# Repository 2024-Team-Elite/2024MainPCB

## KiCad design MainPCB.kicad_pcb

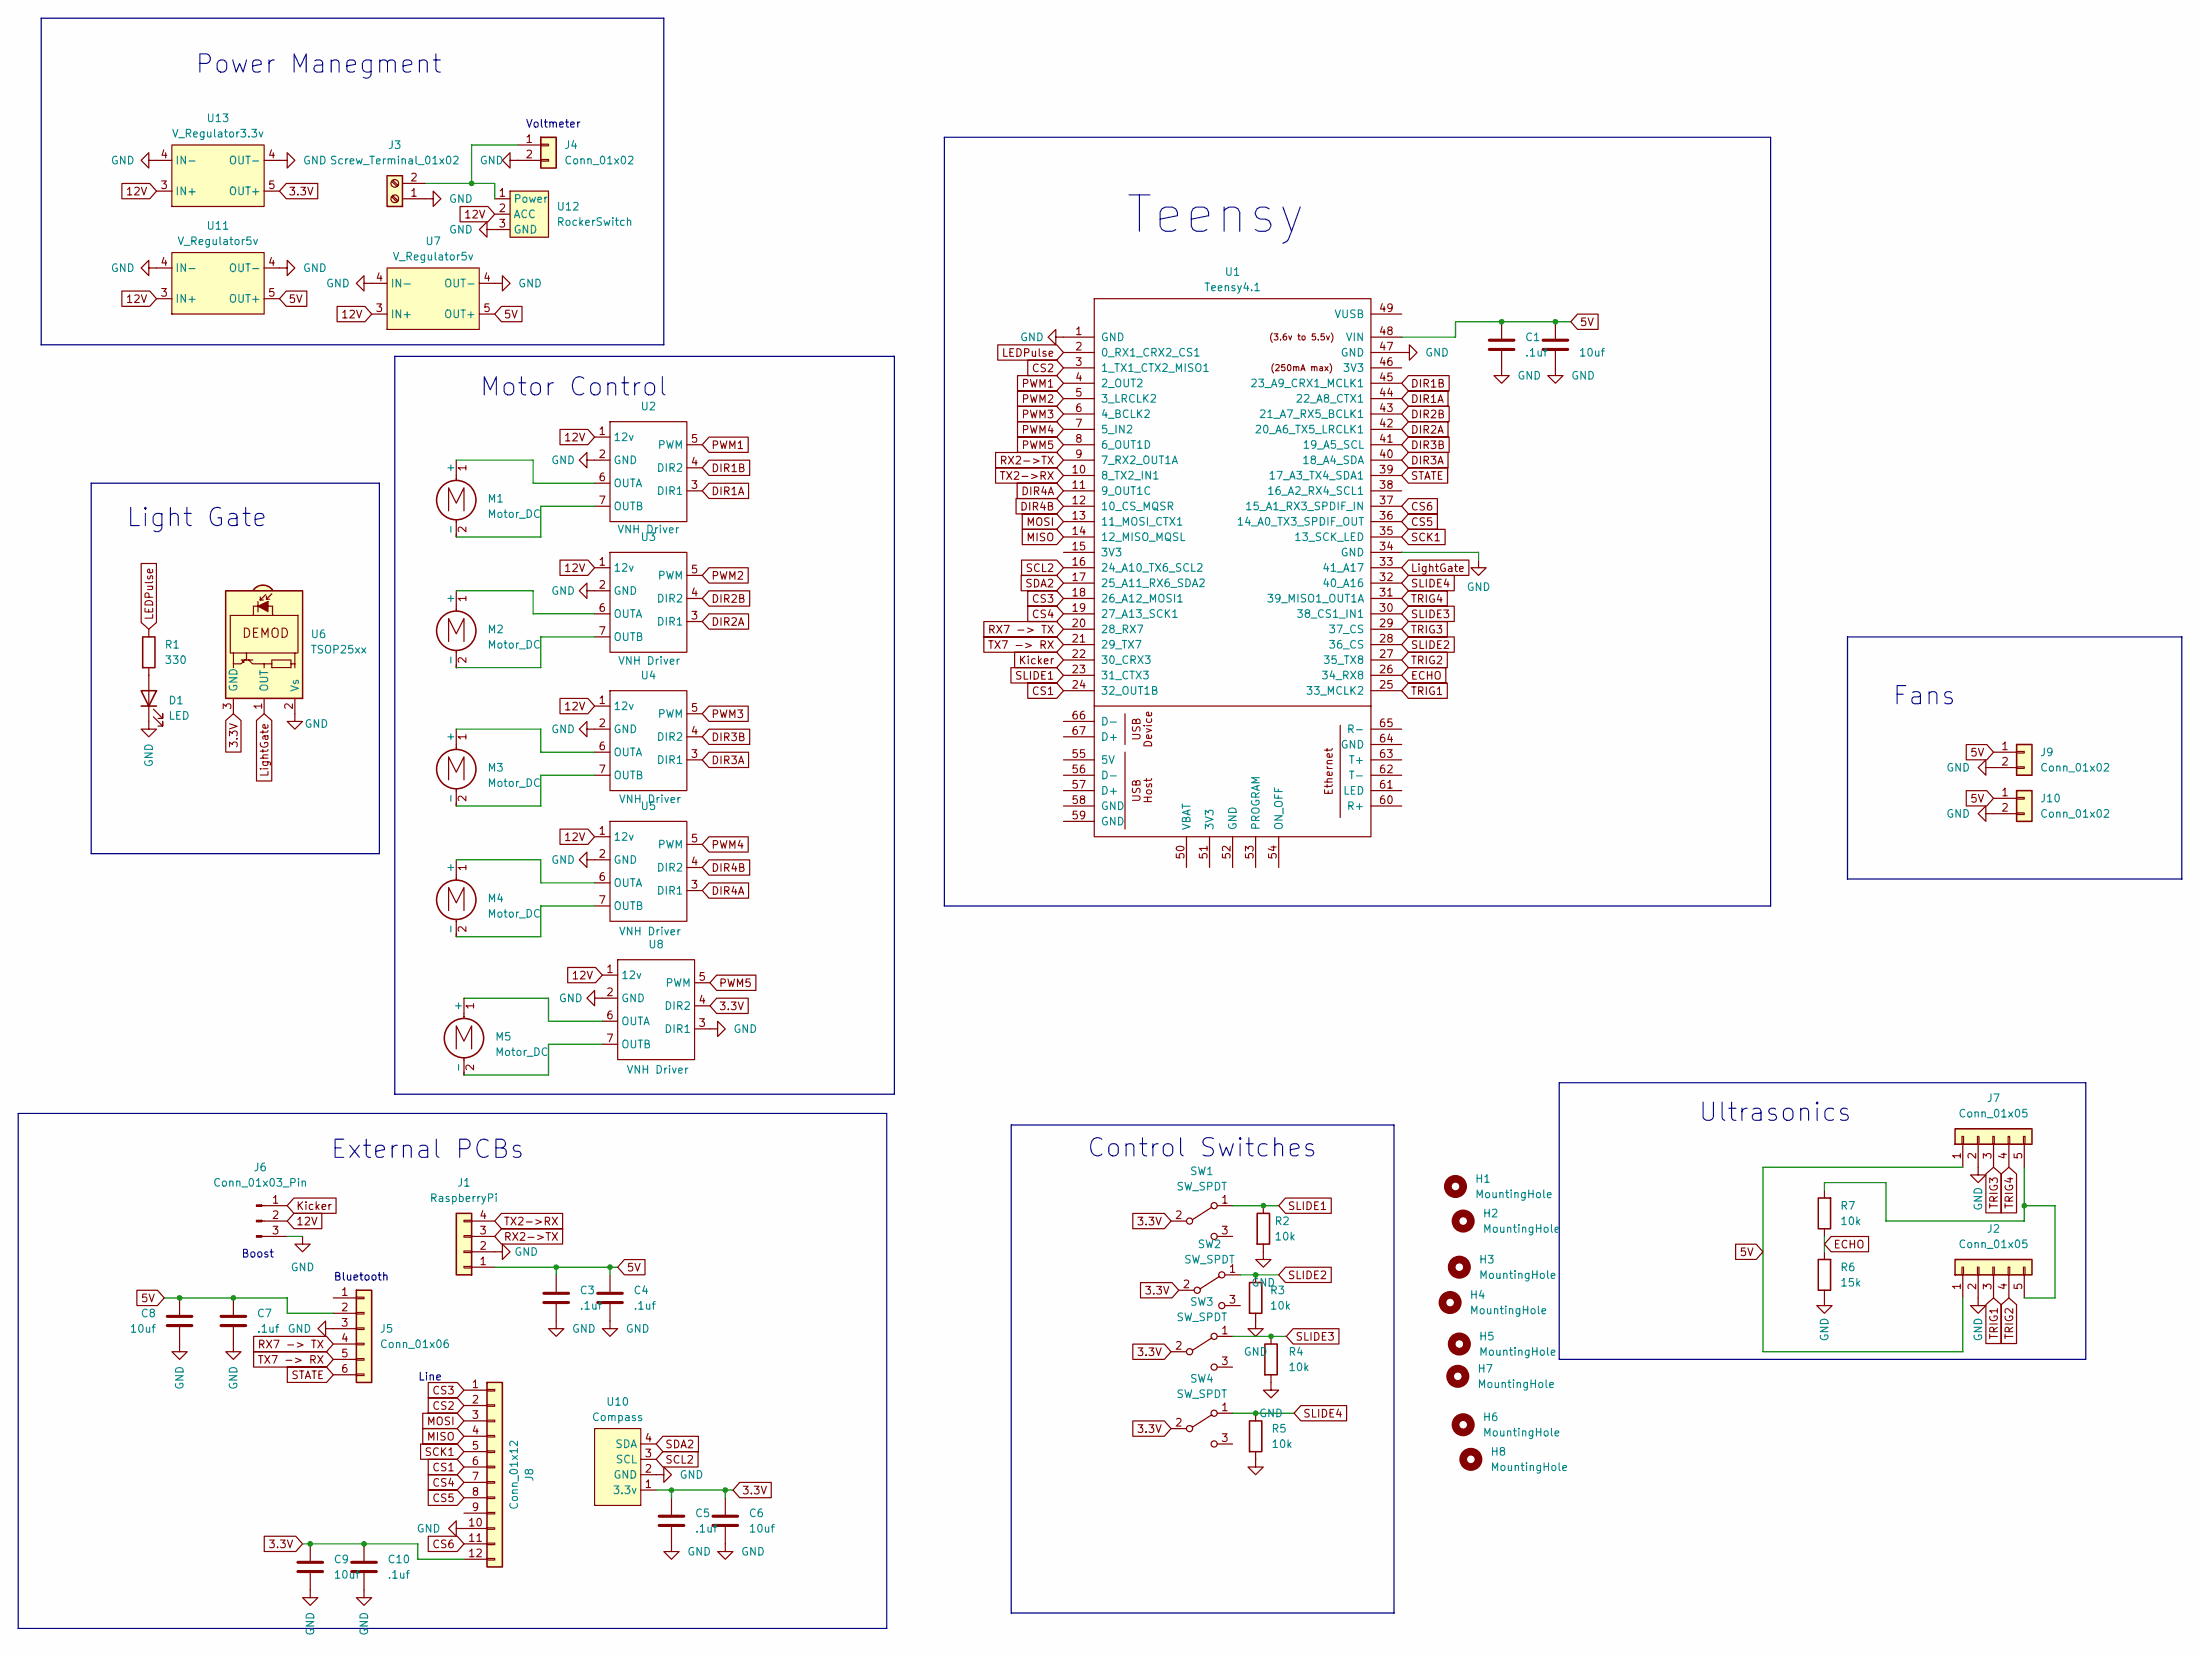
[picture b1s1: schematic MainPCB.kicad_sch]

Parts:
C1, C3, C4, C5, C7, C10: .1uf; C_0805_2012Metric
C2, C6, C8, C9: 10uf; C_0805_2012Metric
D1: LED; JST_XH_B2B-XH-AM_1x02_P2.50mm_Vertical
H1, H2, H3, H4, H5, H6, H7, H8: MountingHole; MountingHole_3.2mm_M3_DIN965_Pad
J1: RaspberryPi; JST_XH_B4B-XH-AM_1x04_P2.50mm_Vertical
J2, J7: Conn_01x05; JST_XH_B5B-XH-A_1x05_P2.50mm_Vertical
J3: Screw_Terminal_01x02; AMASS_XT60-F_1x02_P7.20mm_Vertical
J4: Conn_01x02; PinHeader_2x01_P2.54mm_Vertical
J5: Conn_01x06; PinHeader_1x06_P2.54mm_Vertical
J6: Conn_01x03_Pin; JST_XH_B3B-XH-AM_1x03_P2.50mm_Vertical
J8: Conn_01x12; IDC-Header_2x06_P2.54mm_Vertical
J9, J10: Conn_01x02; PinHeader_1x02_P2.54mm_Vertical
M1, M2, M3, M4, M5: Motor_DC; JST_XH_B2B-XH-AM_1x02_P2.50mm_Vertical
R1: 330; R_Axial_DIN0207_L6.3mm_D2.5mm_P10.16mm_Horizontal
R2, R3, R4, R5: 10k; C_0805_2012Metric_Pad1.18x1.45mm_HandSolder
R6: 15k; C_0805_2012Metric
R7: 10k; C_0805_2012Metric
SW1, SW2, SW3, SW4: SW_SPDT; SPDT_OS102011_CNK
U1: Teensy4.1; Teensy41
U2, U3, U4, U5, U8: VNH Driver; VNHDriver
U6: TSOP25xx; JST_XH_B3B-XH-AM_1x03_P2.50mm_Vertical
U7: V_Regulator5v; Pololu Regulator
U10: Compass; Compass Sensor DFRobot
U11: V_Regulator5v; Pololu5V3.4A
U12: RockerSwitch; RF1-1A-DC-2-B-2
U13: V_Regulator3.3v; Pololu Regulator

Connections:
3.3V: C5.1, C6.1, C9.1, C10.1, J8.12, SW1.2 (B), SW2.2 (B), SW3.2 (B), SW4.2 (B), U6.3 (GND), U8.4 (DIR2), U10.1 (3.3v), U13.5 (OUT+)
5V: C1.1, C2.1, C3.1, C4.1, C7.1, C8.1, J1.1, J2.1, J5.2, J7.1, J9.1, J10.1, U1.48 (VIN), U7.5 (OUT+), U11.5 (OUT+)
12V: J6.2, U2.1 (12v), U3.1 (12v), U4.1 (12v), U5.1 (12v), U7.3 (IN+), U8.1 (12v), U11.3 (IN+), U12.2 (ACC), U13.3 (IN+)
CS1: J8.6, U1.24 (32_OUT1B)
CS2: J8.2, U1.3 (1_TX1_CTX2_MISO1)
CS3: J8.1, U1.18 (26_A12_MOSI1)
CS4: J8.7, U1.19 (27_A13_SCK1)
CS5: J8.8, U1.36 (14_A0_TX3_SPDIF_OUT)
CS6: J8.11, U1.37 (15_A1_RX3_SPDIF_IN)
DIR1A: U1.44 (22_A8_CTX1), U2.3 (DIR1)
DIR1B: U1.45 (23_A9_CRX1_MCLK1), U2.4 (DIR2)
DIR2A: U1.42 (20_A6_TX5_LRCLK1), U3.3 (DIR1)
DIR2B: U1.43 (21_A7_RX5_BCLK1), U3.4 (DIR2)
DIR3A: U1.40 (18_A4_SDA), U4.3 (DIR1)
DIR3B: U1.41 (19_A5_SCL), U4.4 (DIR2)
DIR4A: U1.11 (9_OUT1C), U5.3 (DIR1)
DIR4B: U1.12 (10_CS_MQSR), U5.4 (DIR2)
ECHO: R6.2, R7.1, U1.26 (34_RX8)
GND: C1.2, C2.2, C3.2, C4.2, C5.2, C6.2, C7.2, C8.2, C9.2, C10.2, D1.1 (K), J1.2, J2.2, J3.1, J4.2, J5.3, J6.3, J7.2, J8.10, J9.2, J10.2, R2.2, R3.2, R4.2, R5.2, R6.1, U1.1 (GND), U1.34 (GND), U1.47 (GND), U2.2 (GND), U3.2 (GND), U4.2 (GND), U5.2 (GND), U6.2 (Vs), U7.4 (IN-), U8.2 (GND), U8.3 (DIR1), U10.2 (GND), U11.4 (IN-), U12.3 (GND), U13.4 (OUT-)
Kicker: J6.1, U1.22 (30_CRX3)
LEDPulse: R1.1, U1.2 (0_RX1_CRX2_CS1)
LightGate: U1.33 (41_A17), U6.1 (OUT)
MISO: J8.4, U1.14 (12_MISO_MQSL)
MOSI: J8.3, U1.13 (11_MOSI_CTX1)
unnamed: D1.2 (A), R1.2
unnamed: J2.5, J7.5, R7.2
unnamed: J3.2, J4.1, U12.1 (Power)
unnamed: M1.1 (+), U2.6 (OUTA)
unnamed: M1.2 (-), U2.7 (OUTB)
unnamed: M2.1 (+), U3.6 (OUTA)
unnamed: M2.2 (-), U3.7 (OUTB)
unnamed: M3.1 (+), U4.6 (OUTA)
unnamed: M3.2 (-), U4.7 (OUTB)
unnamed: M4.1 (+), U5.6 (OUTA)
unnamed: M4.2 (-), U5.7 (OUTB)
unnamed: M5.1 (+), U8.6 (OUTA)
unnamed: M5.2 (-), U8.7 (OUTB)
PWM1: U1.4 (2_OUT2), U2.5 (PWM)
PWM2: U1.5 (3_LRCLK2), U3.5 (PWM)
PWM3: U1.6 (4_BCLK2), U4.5 (PWM)
PWM4: U1.7 (5_IN2), U5.5 (PWM)
PWM5: U1.8 (6_OUT1D), U8.5 (PWM)
RX2->TX: J1.3, U1.9 (7_RX2_OUT1A)
RX7 -> TX: J5.4, U1.20 (28_RX7)
SCK1: J8.5, U1.35 (13_SCK_LED)
SCL2: U1.16 (24_A10_TX6_SCL2), U10.3 (SCL)
SDA2: U1.17 (25_A11_RX6_SDA2), U10.4 (SDA)
SLIDE1: R2.1, SW1.1 (A), U1.23 (31_CTX3)
SLIDE2: R3.1, SW2.1 (A), U1.28 (36_CS)
SLIDE3: R4.1, SW3.1 (A), U1.30 (38_CS1_IN1)
SLIDE4: R5.1, SW4.1 (A), U1.32 (40_A16)
STATE: J5.6, U1.39 (17_A3_TX4_SDA1)
TRIG1: J2.3, U1.25 (33_MCLK2)
TRIG2: J2.4, U1.27 (35_TX8)
TRIG3: J7.3, U1.29 (37_CS)
TRIG4: J7.4, U1.31 (39_MISO1_OUT1A)
TX2->RX: J1.4, U1.10 (8_TX2_IN1)
TX7 -> RX: J5.5, U1.21 (29_TX7)

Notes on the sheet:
Line
Fans
Voltmeter
Light Gate
Ultrasonics
External PCBs
Boost
Control Switches
Teensy
Bluetooth
Power Manegment
Motor Control

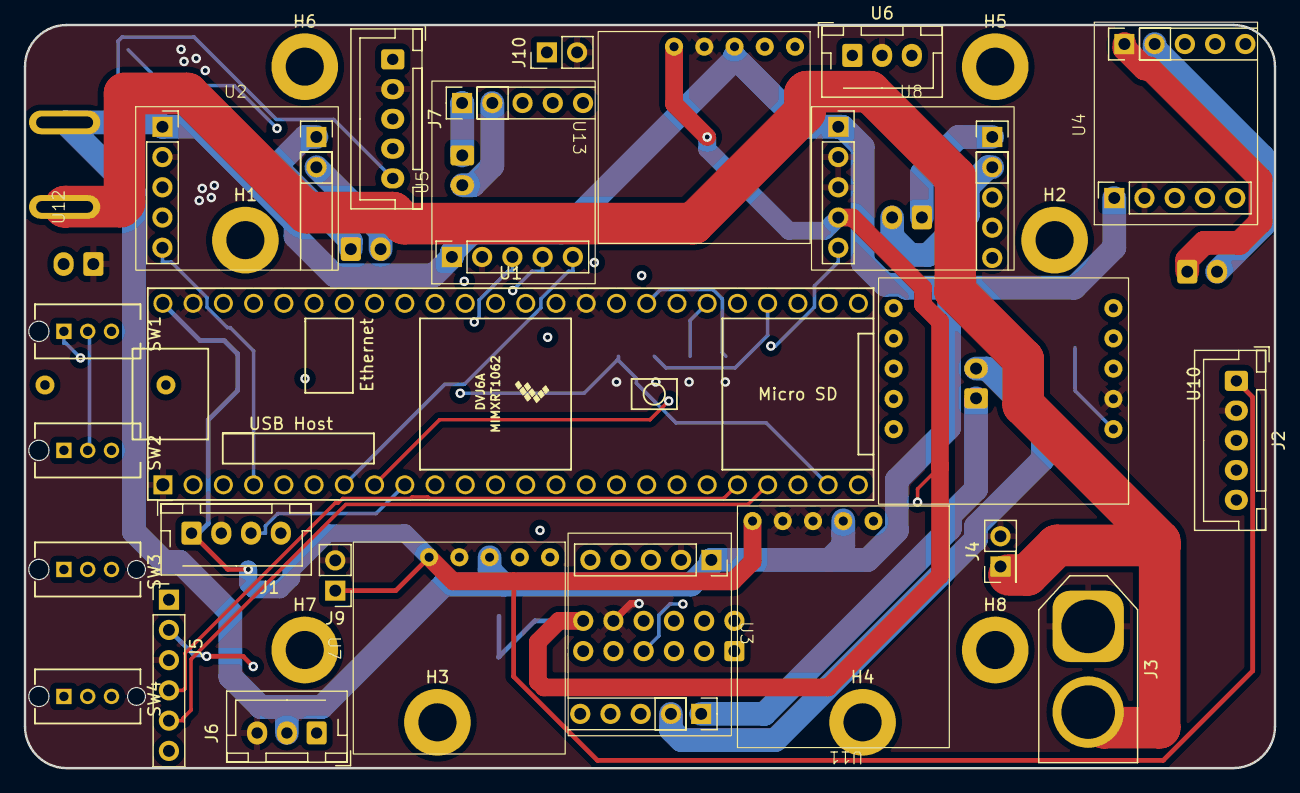
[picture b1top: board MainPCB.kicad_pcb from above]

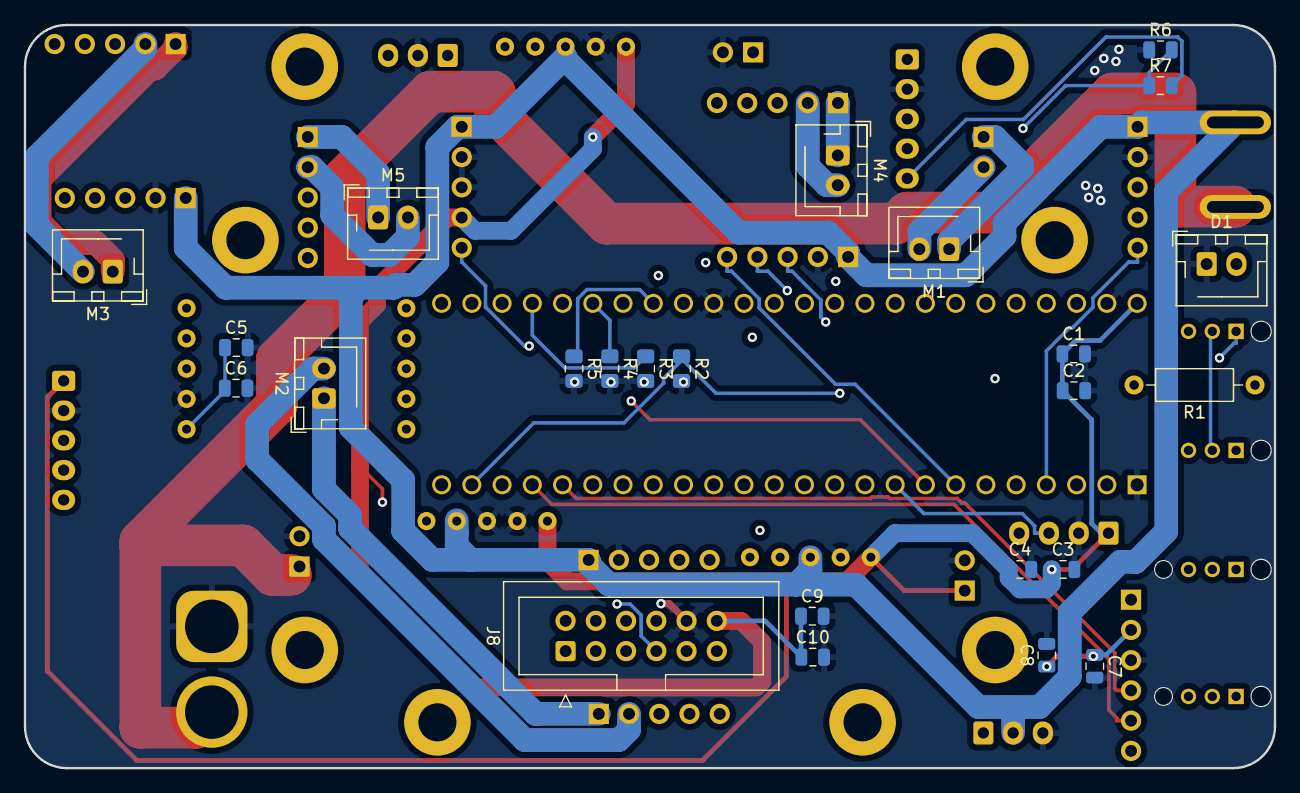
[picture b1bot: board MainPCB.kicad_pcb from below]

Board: 4 copper layers, 105.0 x 62.4 mm, 57 parts (24 on the bottom side), 58 nets.

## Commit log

2024-02-26 Finished Schematic
2024-02-27 Placed Components
2024-02-27 added teensy footprints
2024-02-28 Routed Power Traces
2024-02-28 Finished PCB
    Finished Routing and added thermal zones
2024-02-28 Finished
2024-03-02 Changed Footprints
2024-03-03 done
2024-03-03 done again
2024-03-03 Finshined again
2024-03-03 finished final
2024-03-08 part movement
2024-03-10 Rerouted
2024-03-17 Fixed Trace Widths
2024-04-13 Fixed 5V trace
2024-04-14 Made Changes
2024-04-14 fixed more errors
2024-04-15 Fixed Regulator Pins
2024-04-15 Generated Gerbers
2024-04-15 3.3v thicken
2024-04-21 Changed LED Pulse pin to PWM
2024-04-21 LED pulse to PWM
2024-06-14 Changed Layout
2024-06-15 routing
2024-06-15 moved stuff
2024-06-16 moved more stuff
2024-06-16 Finished Routing
2024-06-16 fixed ultrasonic voltages
2024-06-16 Moved regulators
2024-06-16 fixed 12v power distrubution
2024-06-16 1:17
